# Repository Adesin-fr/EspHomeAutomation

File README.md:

# EspHomeAutomation
Home Automation based on ESP8266 and MQTT

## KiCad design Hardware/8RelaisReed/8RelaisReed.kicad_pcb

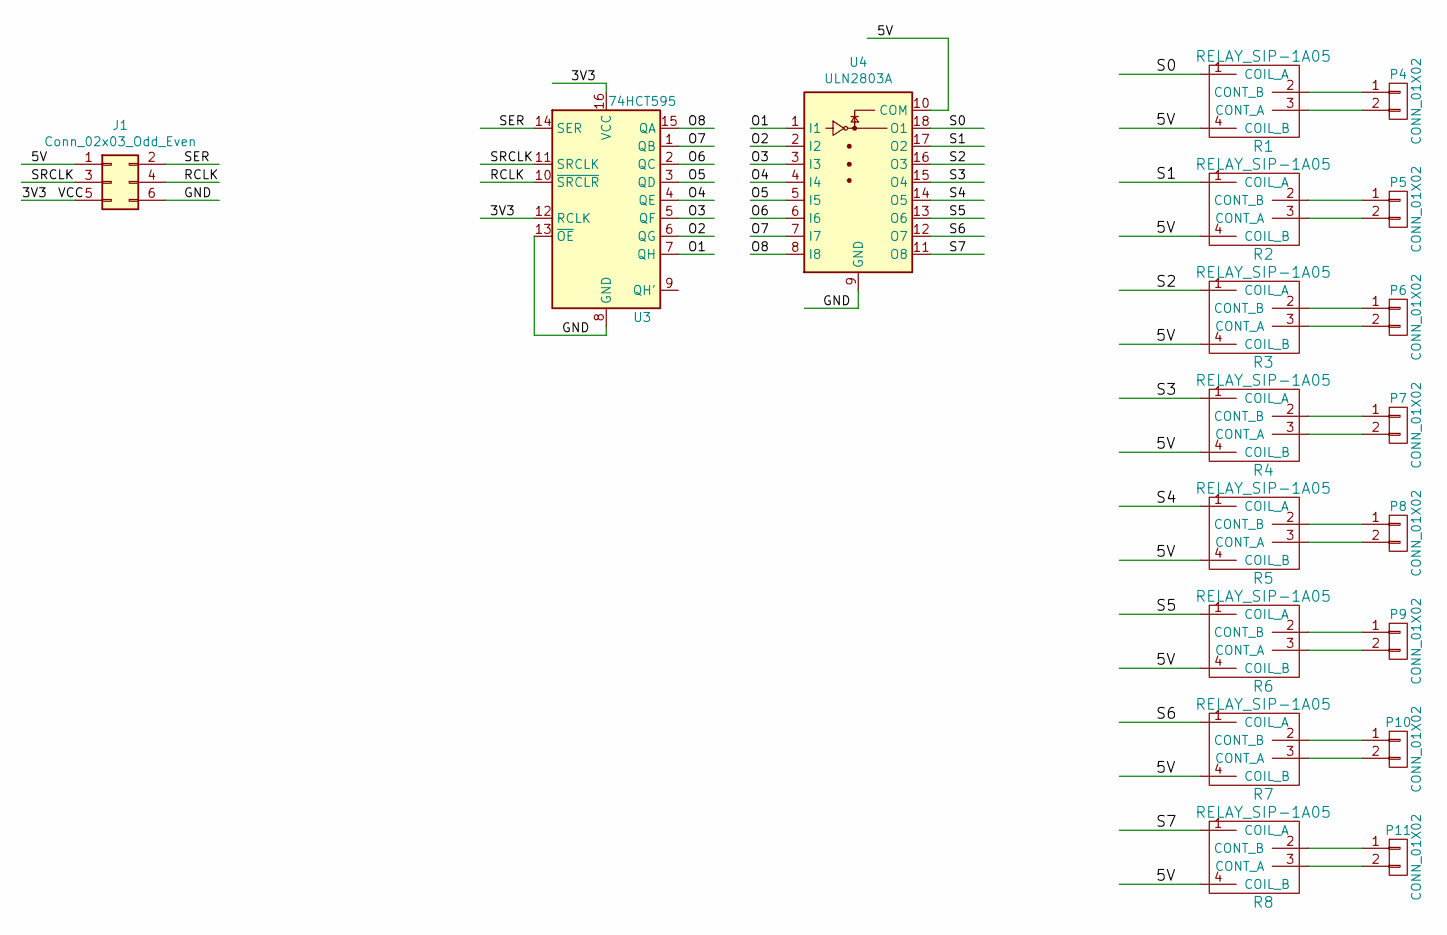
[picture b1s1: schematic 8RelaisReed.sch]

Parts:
J1: Conn_02x03_Odd_Even; PinHeader_2x03_P2.54mm_Vertical
P4, P5, P6, P7, P8, P9, P10, P11: CONN_01X02; bornier2
R1, R2, R3, R4, R5, R6, R7, R8: RELAY_SIP-1A05; SIP4_5.08
U3: 74HCT595; SOIC-16W_5.3x10.2mm_P1.27mm
U4: ULN2803A; SOIC-18W_7.5x11.6mm_P1.27mm

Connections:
/3V3: J1.5, U3.12 (RCLK), U3.16 (VCC)
/5V: J1.1, R1.4 (COIL_B), R2.4 (COIL_B), R3.4 (COIL_B), R4.4 (COIL_B), R5.4 (COIL_B), R6.4 (COIL_B), R7.4 (COIL_B), R8.4 (COIL_B), U4.10 (COM)
/GND: J1.6, U3.8 (GND), U3.13 (~OE), U4.9 (GND)
/O1: U3.7 (QH), U4.1 (I1)
/O2: U3.6 (QG), U4.2 (I2)
/O3: U3.5 (QF), U4.3 (I3)
/O4: U3.4 (QE), U4.4 (I4)
/O5: U3.3 (QD), U4.5 (I5)
/O6: U3.2 (QC), U4.6 (I6)
/O7: U3.1 (QB), U4.7 (I7)
/O8: U3.15 (QA), U4.8 (I8)
/RCLK: J1.4, U3.10 (~SRCLR)
/S0: R1.1 (COIL_A), U4.18 (O1)
/S1: R2.1 (COIL_A), U4.17 (O2)
/S2: R3.1 (COIL_A), U4.16 (O3)
/S3: R4.1 (COIL_A), U4.15 (O4)
/S4: R5.1 (COIL_A), U4.14 (O5)
/S5: R6.1 (COIL_A), U4.13 (O6)
/S6: R7.1 (COIL_A), U4.12 (O7)
/S7: R8.1 (COIL_A), U4.11 (O8)
/SER: J1.2, U3.14 (SER)
/SRCLK: J1.3, U3.11 (SRCLK)
unnamed: P4.1, R1.2 (CONT_B)
unnamed: P4.2, R1.3 (CONT_A)
unnamed: P5.1, R2.2 (CONT_B)
unnamed: P5.2, R2.3 (CONT_A)
unnamed: P6.1, R3.2 (CONT_B)
unnamed: P6.2, R3.3 (CONT_A)
unnamed: P7.1, R4.2 (CONT_B)
unnamed: P7.2, R4.3 (CONT_A)
unnamed: P8.1, R5.2 (CONT_B)
unnamed: P8.2, R5.3 (CONT_A)
unnamed: P9.1, R6.2 (CONT_B)
unnamed: P9.2, R6.3 (CONT_A)
unnamed: P10.1, R7.2 (CONT_B)
unnamed: P10.2, R7.3 (CONT_A)
unnamed: P11.1, R8.2 (CONT_B)
unnamed: P11.2, R8.3 (CONT_A)

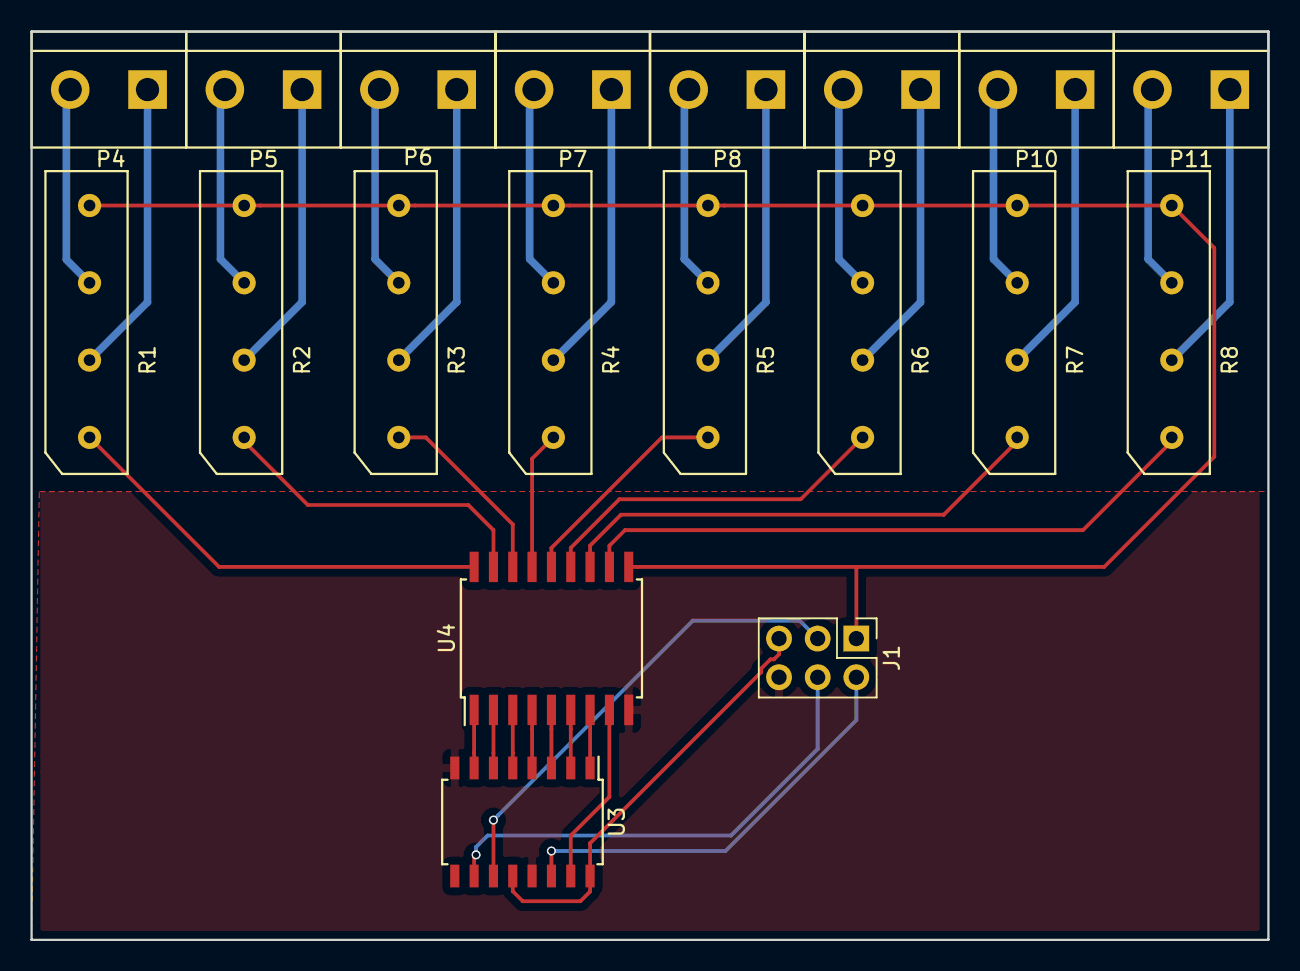
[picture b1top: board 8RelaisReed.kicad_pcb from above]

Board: 2 copper layers, 81.3 x 59.7 mm, 19 parts (0 on the bottom side), 38 nets.

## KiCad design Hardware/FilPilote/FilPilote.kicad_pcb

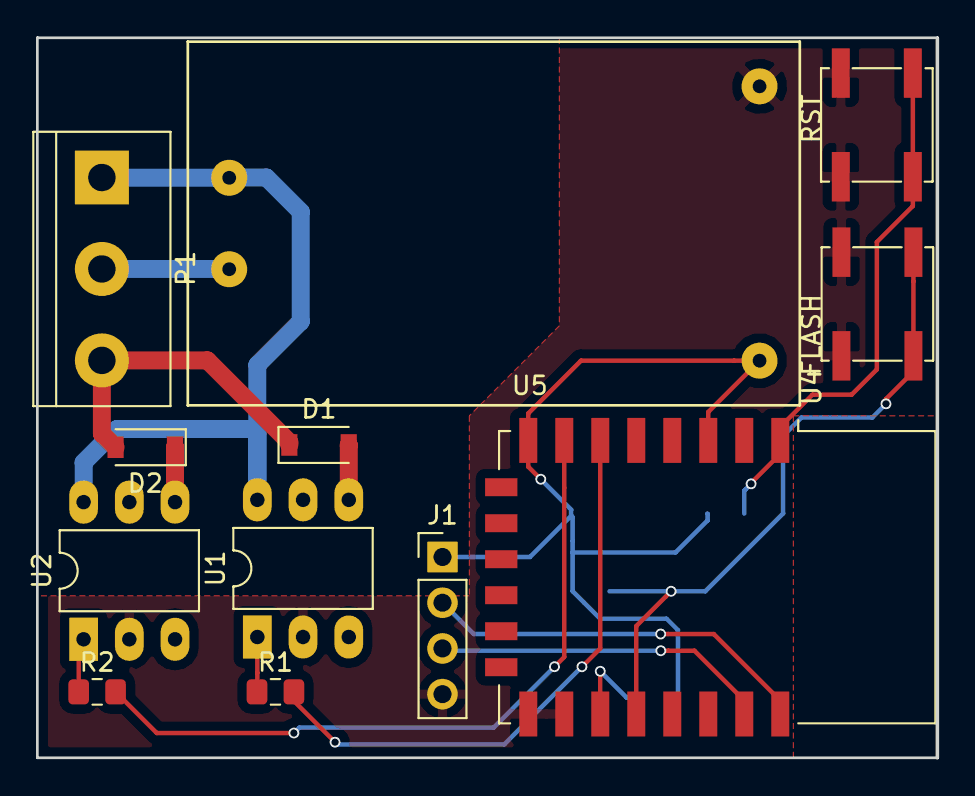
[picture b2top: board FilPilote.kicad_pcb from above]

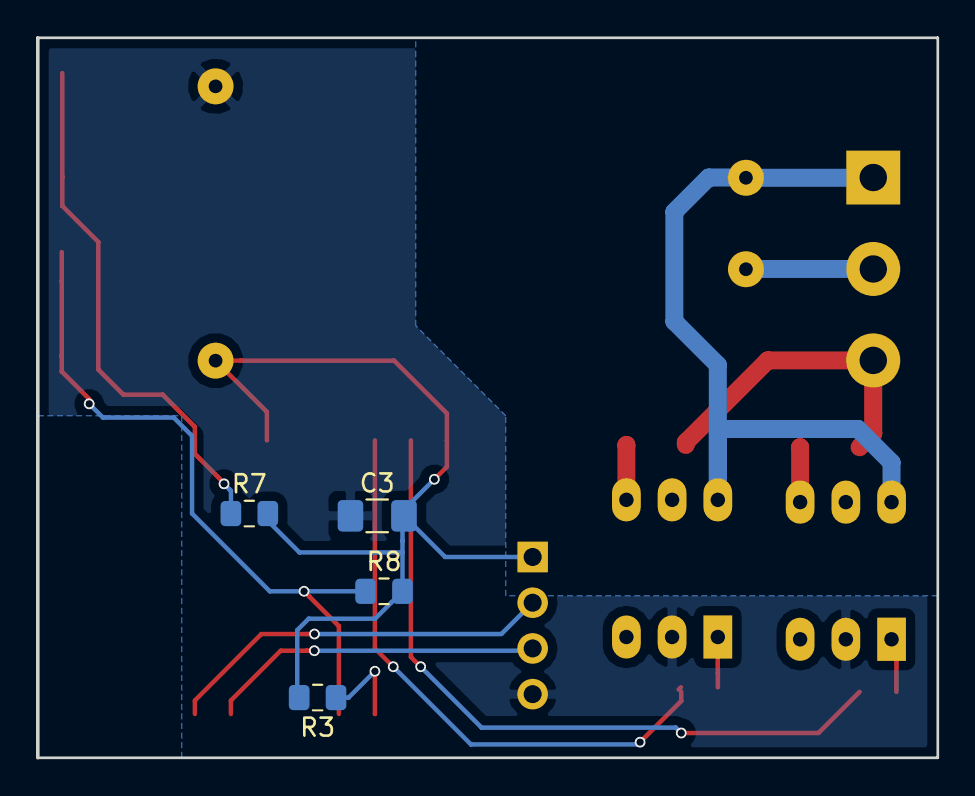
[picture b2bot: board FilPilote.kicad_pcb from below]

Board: 2 copper layers, 50.0 x 40.0 mm, 16 parts (4 on the bottom side), 16 nets.

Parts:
C3: 100nF; C_1206_3216Metric_Pad1.42x1.75mm_HandSolder
D1, D2: D; D_SOD-123
FLASH: FLASH; SW_SPST_EVPBF
J1: Conn_01x04_Male; PinHeader_1x04_P2.54mm_Vertical
P1: CONN_01X03; TerminalBlock_bornier-3_P5.08mm
R1, R2: 270; R_0805_2012Metric_Pad1.15x1.40mm_HandSolder
R3, R7, R8: 10K; R_0805_2012Metric_Pad1.15x1.40mm_HandSolder
RST: RESET; SW_SPST_EVPBF
U1, U2: MOC3041M; DIP-6_W7.62mm_LongPads
U4: ESP-12E
U5: HLK-PM03; HLK-PM01

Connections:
/3V3: C3.2, J1.1, R3.2, R7.2, R8.2, U4.3, U4.8, U5.4
/FP_OUT: D1.1, D2.2, P1.3
/GND: C3.1, FLASH.2, J1.4, RST.1, U1.2, U2.2, U4.15, U4.16, U5.3
/NEUTRE: P1.2, U5.2
/O1: R1.2, U4.6
/O2: R2.2, U4.7
/PH_IN: P1.1, U1.6, U2.6, U5.1
/RXD: J1.3, U4.21
/TXD: J1.2, U4.22
unnamed: D1.2, U1.4
unnamed: D2.1, U2.4
unnamed: R1.1, U1.1
unnamed: R2.1, U2.1
unnamed: R3.1, U4.17
unnamed: R7.1, RST.2, U4.1
unnamed: FLASH.1, R8.1, U4.18

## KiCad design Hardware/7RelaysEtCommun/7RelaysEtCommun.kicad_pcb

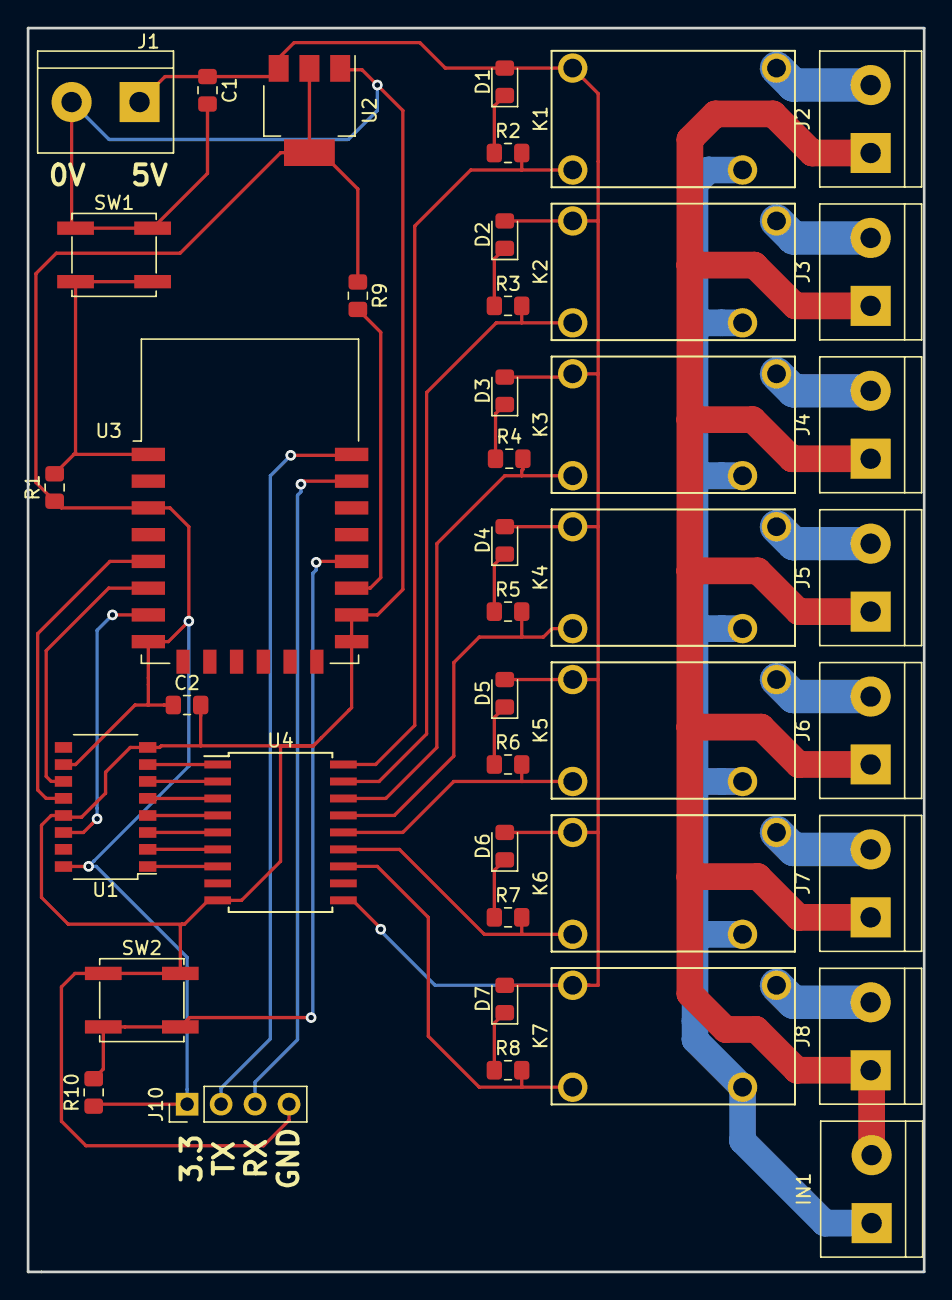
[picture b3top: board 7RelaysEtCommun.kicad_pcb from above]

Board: 2 copper layers, 67.0 x 93.0 mm, 42 parts (0 on the bottom side), 41 nets.

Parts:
C1: 1uF; C_0805_2012Metric_Pad1.15x1.40mm_HandSolder
C2: 100nF; C_0805_2012Metric_Pad1.15x1.40mm_HandSolder
D1, D2, D3, D4, D5, D6, D7: LED; D_0805_2012Metric_Pad1.15x1.40mm_HandSolder
IN1: Conn_01x02_Female; TerminalBlock_bornier-2_P5.08mm
J1: 5VIN; TerminalBlock_bornier-2_P5.08mm
J2, J3, J4, J5, J6, J7, J8: Conn_01x02_Female; TerminalBlock_bornier-2_P5.08mm
J10: ISP; PinHeader_1x04_P2.54mm_Vertical
K1, K2, K3, K4, K5, K6, K7: UMS05-1A80-75L; SANYOU-SJ-S
R1, R9, R10: 10k; R_0805_2012Metric_Pad1.15x1.40mm_HandSolder
R2, R3, R4, R5, R6, R7, R8: 290; R_0805_2012Metric_Pad1.15x1.40mm_HandSolder
SW1: SW_DPST; SW_SPST_EVPBF
SW2: FLASH; SW_SPST_EVPBF
U1: 74HCT595; SOP-16_4.4x10.4mm_P1.27mm
U2: AP1117-33; SOT-223-3_TabPin2
U3: ESP-12F; ESP-12E
U4: ULN2803A; SOIC-18W_7.5x11.6mm_P1.27mm

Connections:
/3V3: C2.1, J10.1, R1.1, R9.1, R10.1, U1.10, U1.16, U2.2, U3.3, U3.8
/5V: C1.1, D1.2, D2.2, D3.2, D4.2, D5.2, D6.2, D7.2, J1.1, K1.2, K2.2, K3.2, K4.2, K5.2, K6.2, K7.2, U2.3, U4.10
/GND: C1.2, C2.2, J1.2, J10.4, SW1.1, SW2.1, U1.8, U1.13, U2.1, U3.15, U3.16, U4.9
/L1: U1.7, U4.1
/L2: U1.6, U4.2
/L3: U1.5, U4.3
/L4: U1.4, U4.4
/L5: U1.3, U4.5
/L6: U1.2, U4.6
/L7: U1.1, U4.7
/NE: IN1.2, J2.1, J3.1, J4.1, J5.1, J6.1, J7.1, J8.1
/OUT1: K1.1, R2.2, U4.18
/OUT2: K2.1, R3.2, U4.17
/OUT3: K3.1, R4.2, U4.16
/OUT4: K4.1, R5.2, U4.15
/OUT5: K5.1, R6.2, U4.14
/OUT6: K6.1, R7.2, U4.13
/OUT7: K7.1, R8.2, U4.12
/PH: IN1.1, K1.4, K2.4, K3.4, K4.4, K5.4, K6.4, K7.4
/RCLK: U1.12, U3.5
/RXD: J10.3, U3.21
/SER: U1.14, U3.7
/SRCLK: U1.11, U3.6
/TXD: J10.2, U3.22
unnamed: D1.1, R2.1
unnamed: D2.1, R3.1
unnamed: D3.1, R4.1
unnamed: D4.1, R5.1
unnamed: D5.1, R6.1
unnamed: D6.1, R7.1
unnamed: D7.1, R8.1
unnamed: J2.2, K1.3
unnamed: J3.2, K2.3
unnamed: J4.2, K3.3
unnamed: J5.2, K4.3
unnamed: J6.2, K5.3
unnamed: J7.2, K6.3
unnamed: J8.2, K7.3
unnamed: R1.2, SW1.2, U3.1
unnamed: R9.2, U3.17
unnamed: R10.2, SW2.2, U3.18

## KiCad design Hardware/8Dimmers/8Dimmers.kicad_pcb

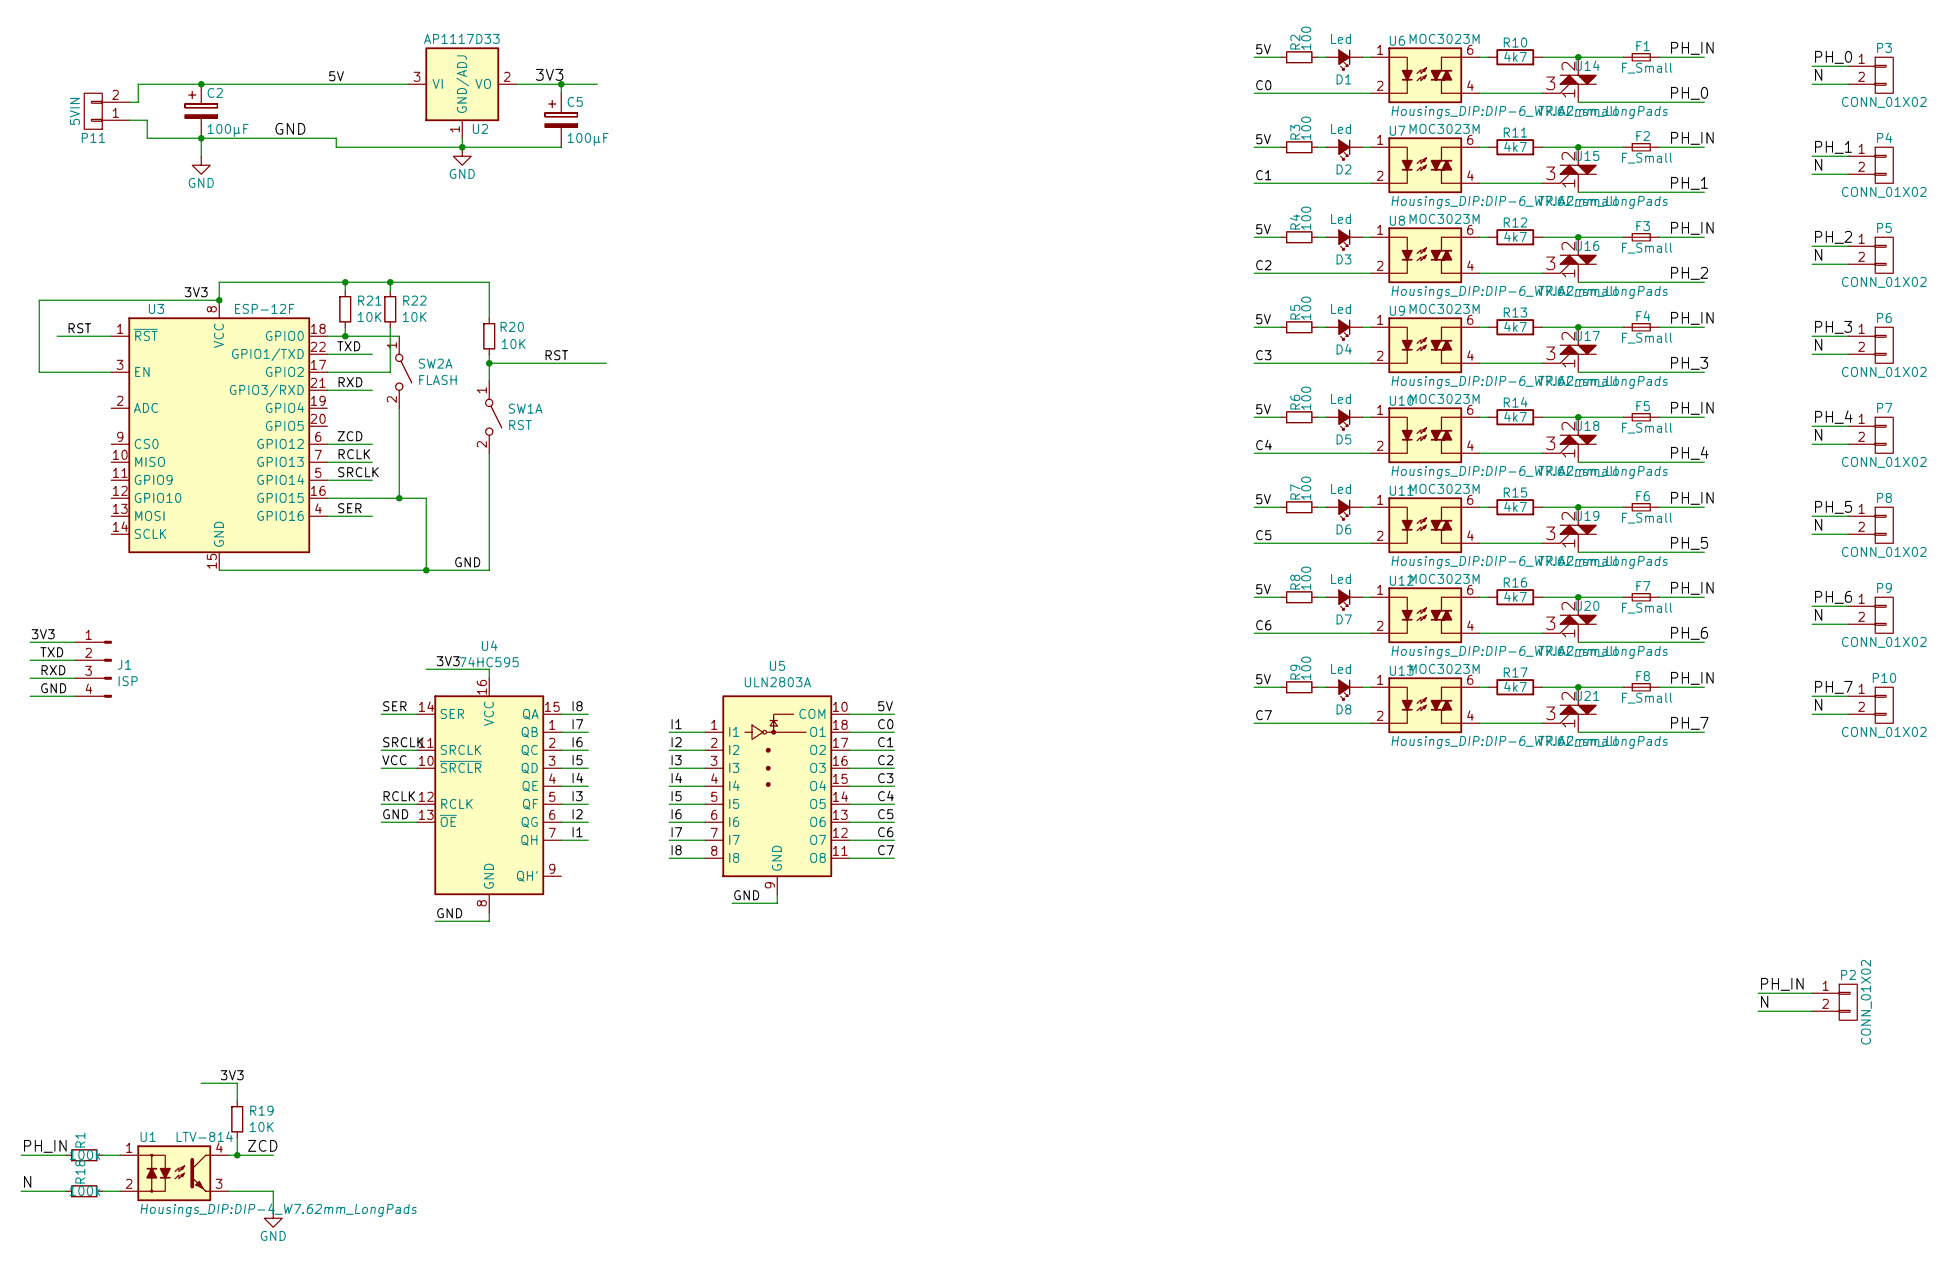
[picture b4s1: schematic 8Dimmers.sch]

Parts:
C2, C5: 100µF; C_0805_2012Metric_Pad1.15x1.40mm_HandSolder
D1, D2, D3, D4, D5, D6, D7, D8: Led; LED_0805_2012Metric_Pad1.15x1.40mm_HandSolder
F1, F2, F3, F4, F5, F6, F7, F8: F_Small; Fuseholder5x20
J1: ISP; PinHeader_1x04_P2.54mm_Vertical
P2, P3, P4, P5, P6, P7, P8, P9, P10: CONN_01X02; TerminalBlock_bornier-2_P5.08mm
P11: 5VIN; TerminalBlock_bornier-2_P5.08mm
R1, R18: 100k; RES35
R2, R3, R4, R5, R6, R7, R8, R9: 100; R_0805_2012Metric_Pad1.15x1.40mm_HandSolder
R10, R11, R12, R13, R14, R15, R16, R17: 4k7; RES35
R19, R20, R21, R22: 10K; R_0805_2012Metric_Pad1.15x1.40mm_HandSolder
SW1: RST; SW_SPST_EVPBF
SW2: FLASH; SW_SPST_EVPBF
U1: LTV-814; DIP-4_W7.62mm_LongPads
U2: AP1117D33; SOT-223-3_TabPin2
U3: ESP-12F; ESP-12E
U4: 74HC595; SOIC-16W_5.3x10.2mm_P1.27mm
U5: ULN2803A; SOIC-18W_7.5x11.6mm_P1.27mm
U6, U7, U8, U9, U10, U11, U12, U13: MOC3023M; DIP-6_W7.62mm_LongPads
U14, U15, U16, U17, U18, U19, U20, U21: TRIAC_small; TO-220

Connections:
/3V3: C5.1, J1.1, R19.1, R20.1, R21.1, R22.1, U2.2 (VO), U3.3 (EN), U3.8 (VCC), U4.16 (VCC)
/5V: C2.1, P11.2, R2.1, R3.1, R4.1, R5.1, R6.1, R7.1, R8.1, R9.1, U2.3 (VI), U5.10 (COM)
/C0: U5.18 (O1), U6.2
/C1: U5.17 (O2), U7.2
/C2: U5.16 (O3), U8.2
/C3: U5.15 (O4), U9.2
/C4: U5.14 (O5), U10.2
/C5: U5.13 (O6), U11.2
/C6: U5.12 (O7), U12.2
/C7: U5.11 (O8), U13.2
/I1: U4.7 (QH), U5.1 (I1)
/I2: U4.6 (QG), U5.2 (I2)
/I3: U4.5 (QF), U5.3 (I3)
/I4: U4.4 (QE), U5.4 (I4)
/I5: U4.3 (QD), U5.5 (I5)
/I6: U4.2 (QC), U5.6 (I6)
/I7: U4.1 (QB), U5.7 (I7)
/I8: U4.15 (QA), U5.8 (I8)
/N: P2.2, P3.2, P4.2, P5.2, P6.2, P7.2, P8.2, P9.2, P10.2, R18.1
/PH_0: P3.1, U14.1
/PH_1: P4.1, U15.1
/PH_2: P5.1, U16.1
/PH_3: P6.1, U17.1
/PH_4: P7.1, U18.1
/PH_5: P8.1, U19.1
/PH_6: P9.1, U20.1
/PH_7: P10.1, U21.1
/PH_IN: F1.2, F2.2, F3.2, F4.2, F5.2, F6.2, F7.2, F8.2, P2.1, R1.1
/RCLK: U3.7 (GPIO13), U4.12 (RCLK)
/RST: R20.2, SW1.1 (A), U3.1 (~RST)
/RXD: J1.3, U3.21 (GPIO3/RXD)
/SER: U3.4 (GPIO16), U4.14 (SER)
/SRCLK: U3.5 (GPIO14), U4.11 (SRCLK)
/TXD: J1.2, U3.22 (GPIO1/TXD)
/ZCD: R19.2, U1.4, U3.6 (GPIO12)
GND: C2.2, C5.2, J1.4, P11.1, SW1.2 (B), SW2.2 (B), U1.3, U2.1 (GND/ADJ), U3.15 (GND), U3.16 (GPIO15), U4.8 (GND), U4.13 (~OE), U5.9 (GND)
unnamed: D1.1 (K), U6.1
unnamed: D1.2 (A), R2.2
unnamed: D2.1 (K), U7.1
unnamed: D2.2 (A), R3.2
unnamed: D3.1 (K), U8.1
unnamed: D3.2 (A), R4.2
unnamed: D4.1 (K), U9.1
unnamed: D4.2 (A), R5.2
unnamed: D5.1 (K), U10.1
unnamed: D5.2 (A), R6.2
unnamed: D6.1 (K), U11.1
unnamed: D6.2 (A), R7.2
unnamed: D7.1 (K), U12.1
unnamed: D7.2 (A), R8.2
unnamed: D8.1 (K), U13.1
unnamed: D8.2 (A), R9.2
unnamed: F1.1, R10.2, U14.2
unnamed: F2.1, R11.2, U15.2
unnamed: F3.1, R12.2, U16.2
unnamed: F4.1, R13.2, U17.2
unnamed: F5.1, R14.2, U18.2
unnamed: F6.1, R15.2, U19.2
unnamed: F7.1, R16.2, U20.2
unnamed: F8.1, R17.2, U21.2
unnamed: R1.2, U1.1
unnamed: R10.1, U6.6
unnamed: R11.1, U7.6
unnamed: R12.1, U8.6
unnamed: R13.1, U9.6
unnamed: R14.1, U10.6
unnamed: R15.1, U11.6
unnamed: R16.1, U12.6
unnamed: R17.1, U13.6
unnamed: R18.2, U1.2
unnamed: R21.2, SW2.1 (A), U3.18 (GPIO0)
unnamed: R22.2, U3.17 (GPIO2)
unnamed: U10.4, U18.3
unnamed: U11.4, U19.3
unnamed: U12.4, U20.3
unnamed: U13.4, U21.3
unnamed: U6.4, U14.3
unnamed: U7.4, U15.3
unnamed: U8.4, U16.3
unnamed: U9.4, U17.3

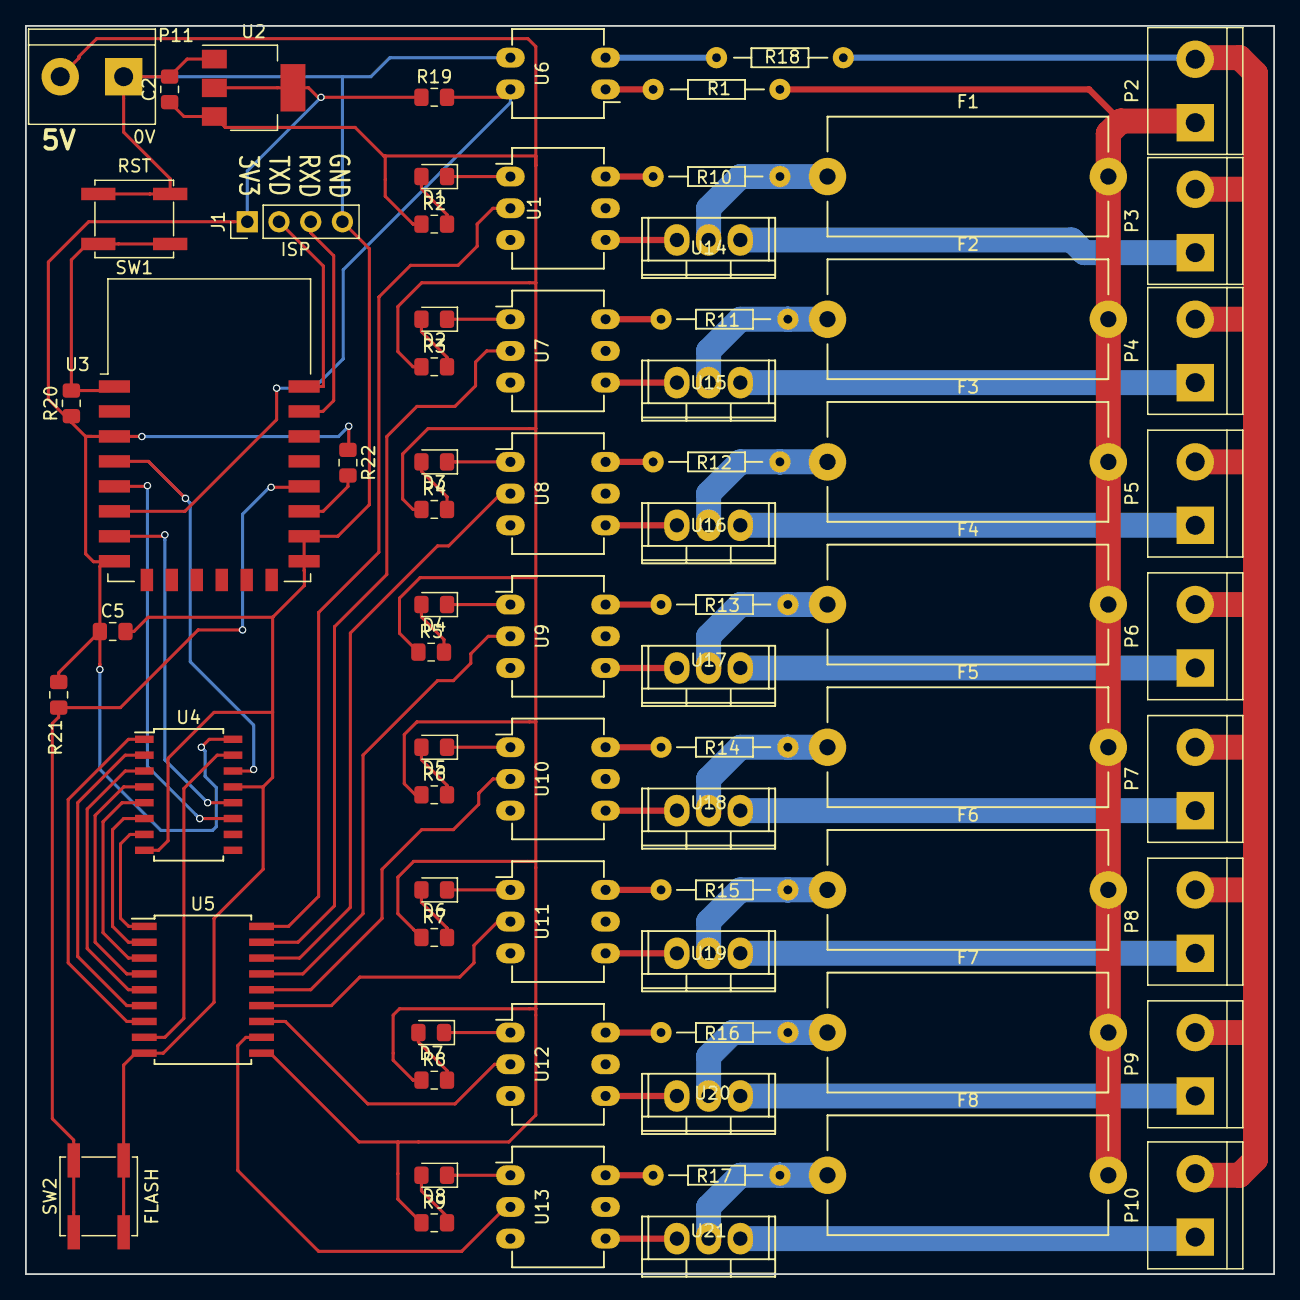
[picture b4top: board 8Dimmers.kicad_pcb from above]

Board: 2 copper layers, 100.0 x 100.0 mm, 74 parts (0 on the bottom side), 80 nets.

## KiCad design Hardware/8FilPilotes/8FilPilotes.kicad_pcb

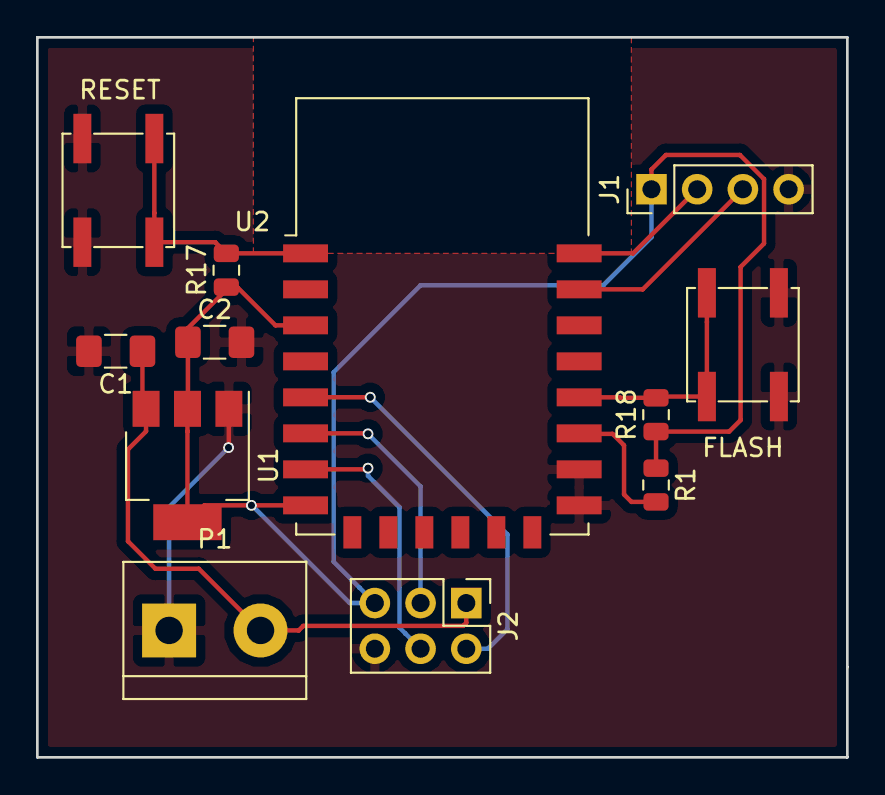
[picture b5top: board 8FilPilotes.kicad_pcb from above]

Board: 2 copper layers, 45.0 x 40.0 mm, 12 parts (0 on the bottom side), 11 nets.

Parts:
C1, C2: 10uF; C_1206_3216Metric_Pad1.42x1.75mm_HandSolder
FLASH: SW_DPST; SW_SPST_EVPBF
J1: Conn_01x04_Male; PinHeader_1x04_P2.54mm_Vertical
J2: Conn_02x03_Odd_Even; PinHeader_2x03_P2.54mm_Vertical
P1: 5VIN; TerminalBlock_bornier-2_P5.08mm
R1, R17, R18: 10k; R_0805_2012Metric
RESET: SW_DPST; SW_SPST_EVPBF
U1: AMS1117; SOT-223-3_TabPin2
U2: ESP-12F; ESP-12E

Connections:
/3V3: C2.1, J1.1, J2.5, R1.1, R17.1, R18.1, U1.2, U2.3, U2.8
/5V: C1.1, J2.1, P1.2, U1.3
/GND: C1.2, C2.2, FLASH.2, J1.4, J2.6, P1.1, RESET.1, U1.1, U2.15, U2.16
/RCLK: J2.4, U2.7
/RXD: J1.3, U2.21
/SER: J2.2, U2.5
/SRCLK: J2.3, U2.6
/TXD: J1.2, U2.22
unnamed: R1.2, U2.17
unnamed: R17.2, RESET.2, U2.1
unnamed: FLASH.1, R18.2, U2.18

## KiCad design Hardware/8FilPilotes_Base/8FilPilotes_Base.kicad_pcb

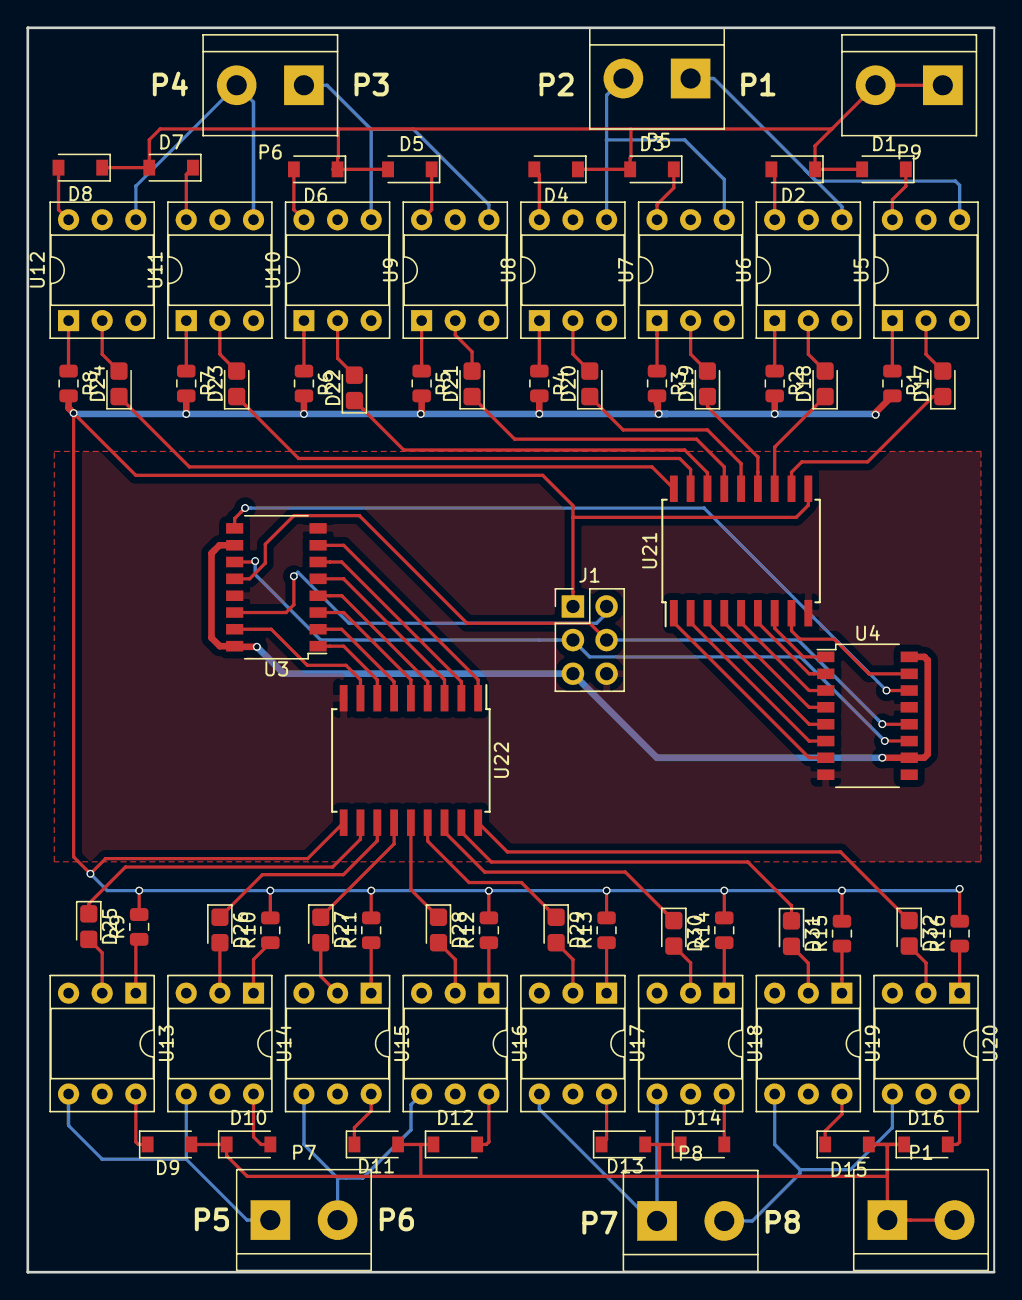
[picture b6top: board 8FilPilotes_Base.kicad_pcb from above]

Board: 2 copper layers, 73.0 x 94.0 mm, 75 parts (0 on the bottom side), 96 nets.

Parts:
D1, D2, D3, D4, D5, D6, D7, D8, D9, D10, D11, D12, D13, D14, D15, D16: D; SOD-123
D17, D18, D19, D20, D21, D22, D23, D24, D25, D26, D27, D28, D29, D30, D31, D32: LED_Small; LED_0805_2012Metric_Castellated
J1: Conn_02x03_Odd_Even; PinHeader_2x03_P2.54mm_Vertical
P1, P5, P6, P7, P8, P9: CONN_01X02; TerminalBlock_bornier-2_P5.08mm
R1, R2, R3, R4, R5, R6, R7, R8, R9, R10, R11, R12, R13, R14, R15, R16: 200; R_0805_2012Metric
U3, U4: 74HC595; SOP-16_4.4x10.4mm_P1.27mm
U5, U6, U7, U8, U9, U10, U11, U12, U13, U14, U15, U16, U17, U18, U19, U20: MOC3043; DIP-6_W7.62mm_Socket
U21, U22: ULN2803A; SOIC-18W_7.5x11.6mm_P1.27mm

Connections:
/5V: J1.1, R1.2, R2.2, R3.2, R4.2, R5.2, R6.2, R7.2, R8.2, R9.2, R10.2, R11.2, R12.2, R13.2, R14.2, R15.2, R16.2, U21.10, U22.10
/FP1: P5.1, U5.4, U6.4
/FP1_A: D17.1, U21.11
/FP1_B: D18.1, U21.12
/FP2: P5.2, U7.4, U8.4
/FP2_A: D19.1, U21.13
/FP2_B: D20.1, U21.14
/FP3: P6.1, U9.4, U10.4
/FP3_A: D21.1, U21.15
/FP3_B: D22.1, U21.16
/FP4: P6.2, U11.4, U12.4
/FP4_A: D23.1, U21.17
/FP4_B: D24.1, U21.18
/FP5: P7.1, U13.4, U14.4
/FP5_A: D25.1, U22.11
/FP5_B: D26.1, U22.12
/FP6: P7.2, U15.4, U16.4
/FP6_A: D27.1, U22.13
/FP6_B: D28.1, U22.14
/FP7: P8.1, U17.4, U18.4
/FP7_A: D29.1, U22.15
/FP7_B: D30.1, U22.16
/FP8: P8.2, U19.4, U20.4
/FP8_A: D31.1, U22.17
/FP8_B: D32.1, U22.18
/I1: U4.7, U21.1
/I2: U4.6, U21.2
/I3: U4.5, U21.3
/I4: U4.4, U21.4
/I5: U4.3, U21.5
/I6: U4.2, U21.6
/I7: U4.1, U21.7
/I8: U4.15, U21.8
/I9: U3.7, U22.1
/I10: U3.6, U22.2
/I11: U3.5, U22.3
/I12: U3.4, U22.4
/I13: U3.3, U22.5
/I14: U3.2, U22.6
/I15: U3.1, U22.7
/I16: U3.15, U22.8
/PH_IN: D1.2, D2.1, D3.2, D4.1, D5.2, D6.1, D7.2, D8.1, D9.2, D10.1, D11.2, D12.1, D13.2, D14.1, D15.2, D16.1, P1.1, P1.2, P9.1, P9.2
/RCLK: J1.4, U3.12, U4.12
/SER: J1.2, U3.14
/SRCLK: J1.3, U3.11, U4.11
GND: J1.6, U3.8, U3.13, U4.8, U4.13, U21.9, U22.9
unnamed: D1.1, U5.6
unnamed: D2.2, U6.6
unnamed: D3.1, U7.6
unnamed: D4.2, U8.6
unnamed: D5.1, U9.6
unnamed: D6.2, U10.6
unnamed: D7.1, U11.6
unnamed: D8.2, U12.6
unnamed: D9.1, U13.6
unnamed: D10.2, U14.6
unnamed: D11.1, U15.6
unnamed: D12.2, U16.6
unnamed: D13.1, U17.6
unnamed: D14.2, U18.6
unnamed: D15.1, U19.6
unnamed: D16.2, U20.6
unnamed: D17.2, U5.2
unnamed: D18.2, U6.2
unnamed: D19.2, U7.2
unnamed: D20.2, U8.2
unnamed: D21.2, U9.2
unnamed: D22.2, U10.2
unnamed: D23.2, U11.2
unnamed: D24.2, U12.2
unnamed: D25.2, U13.2
unnamed: D26.2, U14.2
unnamed: D27.2, U15.2
unnamed: D28.2, U16.2
unnamed: D29.2, U17.2
unnamed: D30.2, U18.2
unnamed: D31.2, U19.2
unnamed: D32.2, U20.2
unnamed: R1.1, U5.1
unnamed: R2.1, U6.1
unnamed: R3.1, U7.1
unnamed: R4.1, U8.1
unnamed: R5.1, U9.1
unnamed: R6.1, U10.1
unnamed: R7.1, U11.1
unnamed: R8.1, U12.1
unnamed: R9.1, U13.1
unnamed: R10.1, U14.1
unnamed: R11.1, U15.1
unnamed: R12.1, U16.1
unnamed: R13.1, U17.1
unnamed: R14.1, U18.1
unnamed: R15.1, U19.1
unnamed: R16.1, U20.1
unnamed: U3.9, U4.14
VCC: J1.5, U3.10, U3.16, U4.10, U4.16

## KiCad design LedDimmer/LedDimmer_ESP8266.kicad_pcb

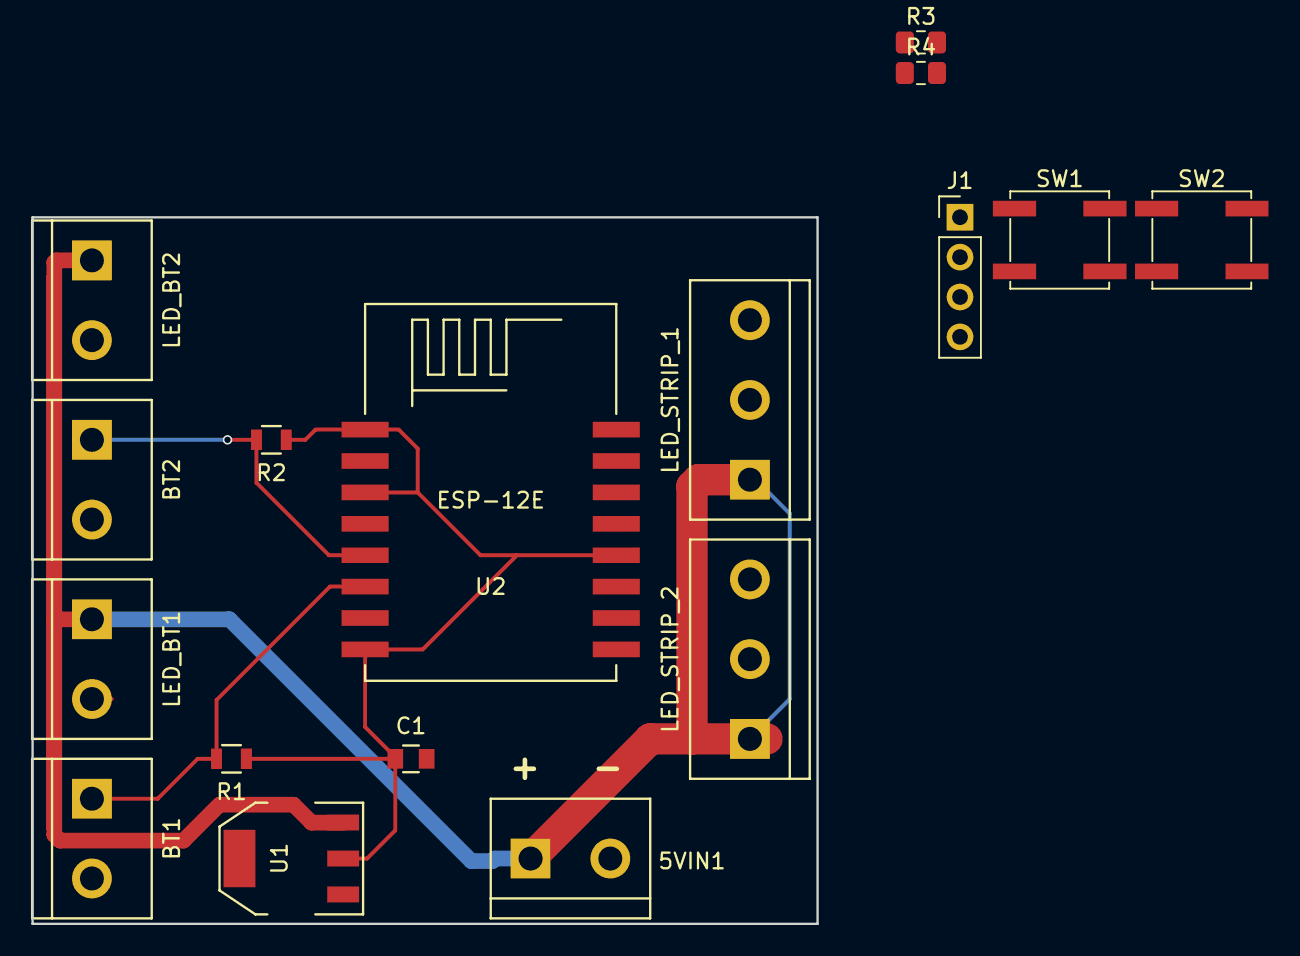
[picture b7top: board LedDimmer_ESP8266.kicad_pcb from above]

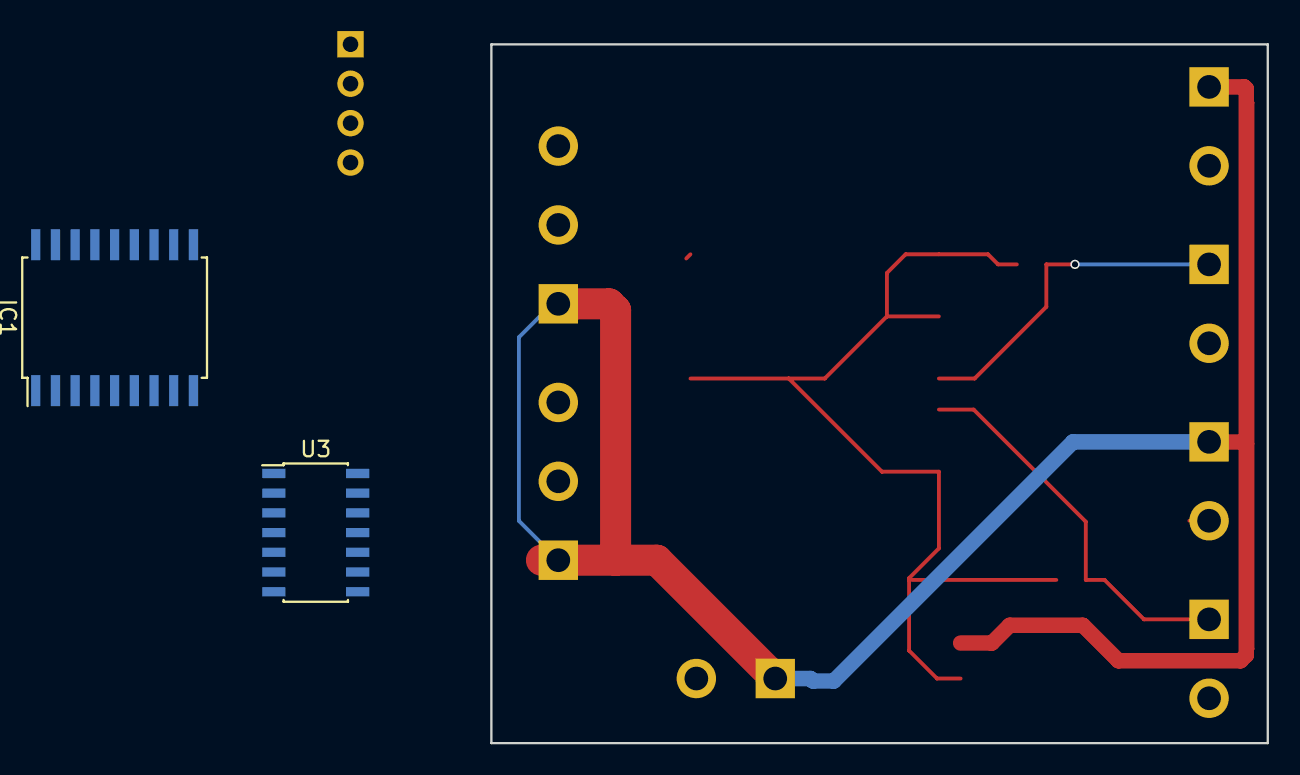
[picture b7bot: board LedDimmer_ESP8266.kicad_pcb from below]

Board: 2 copper layers, 50.0 x 45.0 mm, 19 parts (2 on the bottom side), 17 nets.

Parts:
5VIN1: CONN_01X02; bornier2
BT1, BT2: CONN_01X02; bornier2
C1: 100nF; C_0805
IC1: ULN2803A; SOIC-18_7.5x11.6mm_Pitch1.27mm
J1: ISP; PinHeader_1x04_P2.54mm_Vertical
LED_BT1, LED_BT2: CONN_01X02; bornier2
LED_STRIP_1, LED_STRIP_2: CONN_01X03; bornier3
R1, R2: 10k; R_0805
R3, R4: 10k; R_0805_2012Metric_Pad1.15x1.40mm_HandSolder
SW1: RESET; SW_SPST_EVPBF
SW2: FLASH; SW_SPST_EVPBF
U1: AP1117D33; SOT-223
U2: ESP-12E; ESP-12
U3: 74LS125; SOIC-14_3.9x8.7mm_Pitch1.27mm

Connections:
/3V3: C1.1, J1.1, R1.1, R2.1, R4.1, U1.2, U2.3, U2.8
/BTN1: BT1.1, R1.2, U2.6
/BTN2: BT2.1, R2.2, U2.5
/L1: IC1.1, U2.11
/L2: IC1.2, U2.7
/LED1: IC1.18, LED_BT1.2
/LED2: IC1.17, LED_BT2.2
/O1: U2.14, U3.2
/O2: U2.13, U3.5
/OUT1: LED_STRIP_1.2, U3.3
/OUT2: LED_STRIP_2.2, U3.6
/RST: R3.2, SW1.1, U2.1
/RXD: J1.3, U2.15
/TXD: J1.2, U2.16
GND: 5VIN1.2, BT1.2, BT2.2, C1.2, IC1.9, J1.4, LED_STRIP_1.3, LED_STRIP_2.3, SW1.2, SW2.2, U1.1, U2.9, U2.10, U3.1, U3.4, U3.7
unnamed: R4.2, SW2.1, U2.12
VCC: 5VIN1.1, IC1.10, LED_BT1.1, LED_BT2.1, LED_STRIP_1.1, LED_STRIP_2.1, U1.3, U3.14
